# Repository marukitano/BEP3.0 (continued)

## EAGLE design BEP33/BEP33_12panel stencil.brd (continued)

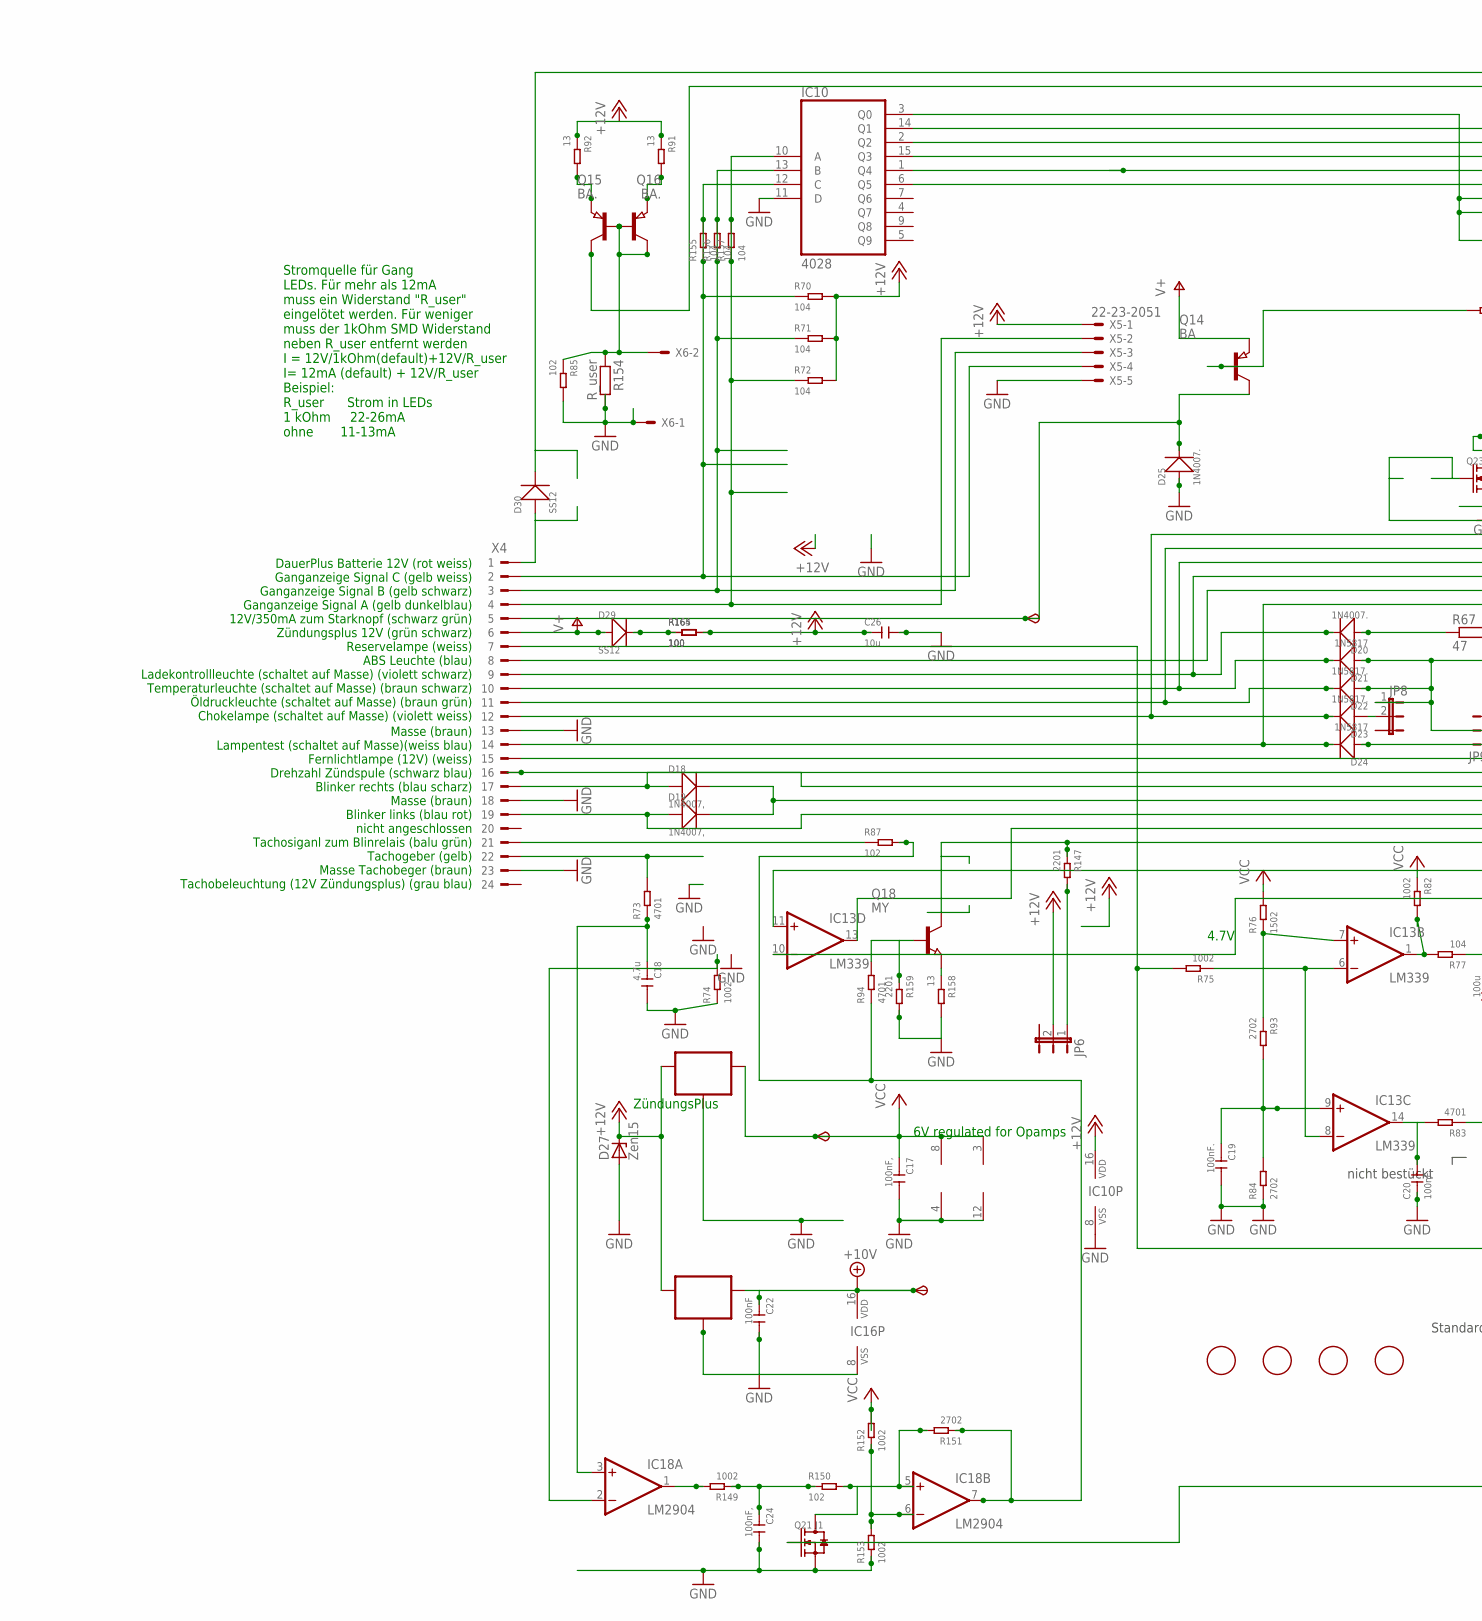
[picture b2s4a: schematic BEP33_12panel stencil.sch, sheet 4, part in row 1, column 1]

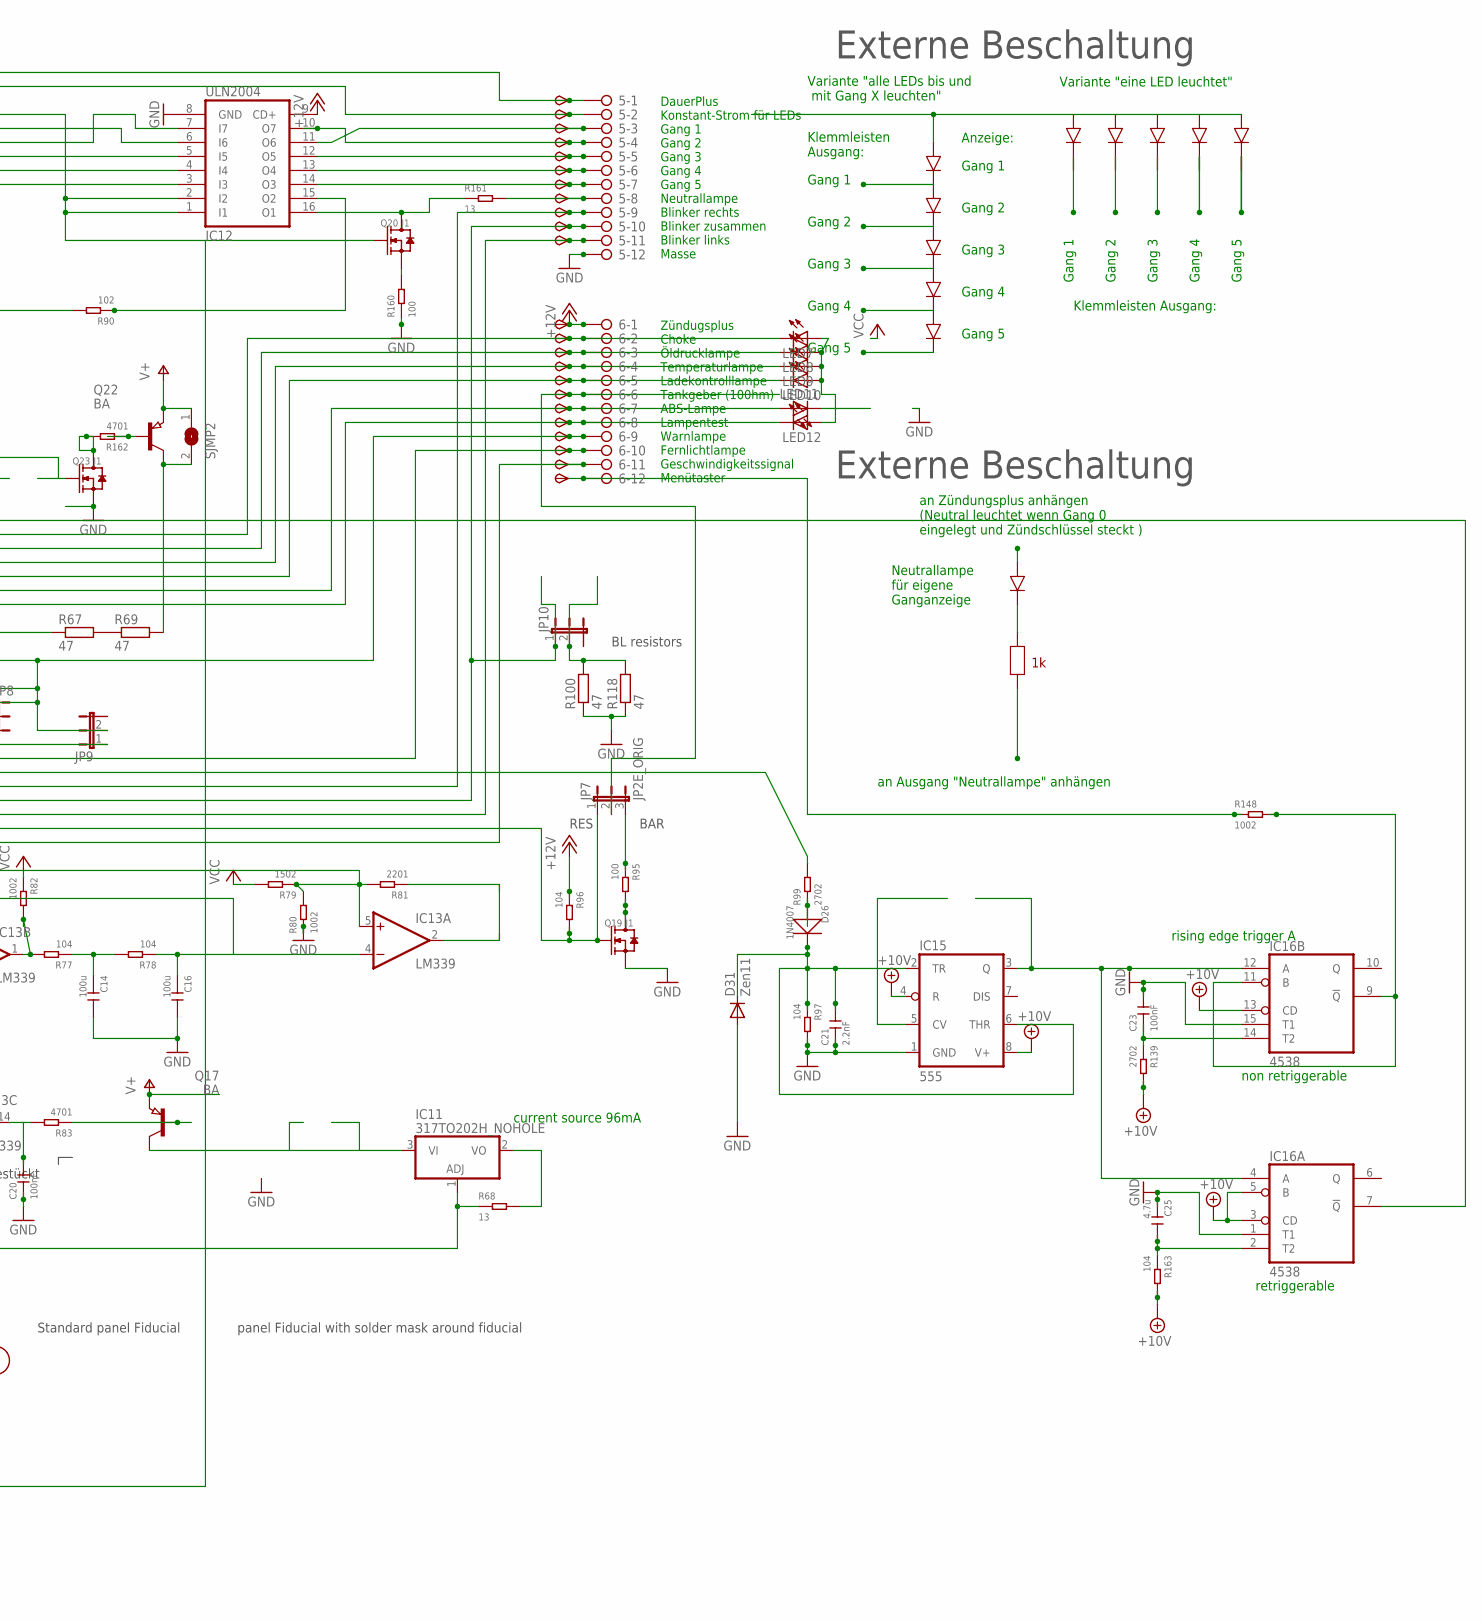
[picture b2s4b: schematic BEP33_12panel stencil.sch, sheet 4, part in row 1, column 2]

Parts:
5, 6: 2081-1132; 12-PIN
6V2, 10V2: TPSB2.0; B2.0
C14, C16: 100u; C1206
C17, C24: 100nF,; C0805
C18, C25: 4.7u; C0805
C19, C20: 100nF.; C0805
C21: 2.2nF; C0805
C22, C23: 100nF; C0805
C26: 10u; C1206
D18, D19: 1N4007,; DO-214AC
D20, D25: 1N4007.; DO-214AC
D21, D24: 1N5817; DO-214AC_SLIM
D22, D23: 1N5817.; DO-214AC_SLIM
D26: 1N4007; DO-214AC
D27: Zen15; DO214AA
D29, D30: SS12; DO-214AC_SLIM
D31: Zen11; SOD-123_MINI-SMA
FID7, FID8, FID9, FID10: FIDUCIAL; FIDUCIAL_1MM
IC10: 4028; SO16
IC11: 317TO202H_NOHOLE; TO220H_NOHOLE
IC12: ULN2004; SO16
IC13: LM339; SO14
IC14: 78L06; SOT89_ROUND
IC15: 555; SO08
IC16: 4538; SO16
IC17: 78L10; SOT89_ROUND
IC18: LM2904; SO08
JP6, JP8, JP9, JP10: JP2EJP2_SMALLPADS; JP2_SMALLPADS
JP7: JP2E_ORIG; JP2_ORIG_SMALLPADS
LED7, LED8, LED9, LED10, LED11, LED12: LEDLD260; LD260
Q14, Q17, Q22: BA; SOT89
Q15, Q16: BA.; SOT89
Q18: MY; SOT89
Q19, Q20, Q21, Q23: J1; SOT-23
R67, R69, R100, R118: 47; V235/17_1MM
R68, R91, R92, R158, R161: 13; R1206
R70, R71, R72, R77, R78, R96, R97, R155, R156, R157, R163: 104; R0805
R73, R83, R94, R162: 4701; R0805
R74, R75, R80, R82, R148, R149, R152, R153: 1002; R0805
R76, R79: 1502; R0805
R81, R147, R159: 2201; R0805
R84, R93, R99, R139, R151: 2702; R0805
R85, R87, R90, R150: 102; R0805
R95, R160, R164, R165: 100; R0805
R154: R_user; R0805
SJMP2: SJ
START2: TPSB2.0; B2.0
TP47, TP48, TP49, TP50, TP51, TP52, TP53, TP54, TP55, TP56, TP57, TP58, TP59, TP60, TP61, TP62, TP63, TP64, TP66, TP67, TP68, TP69: TPSB2.0; B2.0
TP65: TPSB1,27; B1,27
X4: CON_BMWV2; 24-PIN_V2
X5: 22-23-2051
X6: 22-23-2021

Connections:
+10V: 10V2.TP, C22.1, IC15.4 (R), IC15.8 (V+), IC16.3 (CD), IC16.5 (B), IC16.13 (CD), IC16.16 (VDD), IC17.1 (OUT), R139.2, R163.2; also elsewhere on the board
+12V: 6.1, C26.1, D27.C, IC10.16 (VDD), IC12.9 (CD+), IC14.3 (IN), IC17.3 (IN), JP6.2, R70.2, R71.2, R72.2, R91.1, R92.1, R96.1, R164.2, R165.2, TP68.TP, X5.1; also elsewhere on the board
+12V3: 6.11, Q18.2 (C), R147.1, TP67.TP
GND: 5.12, C14.2, C16.2, C17.2, C18.2, C19.2, C20.1, C21.1, C22.2, C23.2, C24.2, C25.1, C26.2, D25.1 (+), D27.A, D31.A, IC10.8 (VSS), IC10.11 (D), IC12.8 (GND), IC13.12 (GND), IC14.2 (GND), IC14.2@1 (GND), IC15.1 (GND), IC16.1 (T1), IC16.8 (VSS), IC16.15 (T1), IC17.2 (GND), IC17.2@1 (GND), IC18.4 (V-), Q19.2 (S), Q21.2 (S), Q23.2 (S), R74.1, R80.1, R84.1, R85.2, R97.2, R100.1, R118.1, R153.1, R154.2, R158.2, R159.2, R160.1, X4.13, X4.18, X4.23, X5.5, X6.1; also elsewhere on the board
unnamed: R67.2, R69.1
unnamed: 6.9, D21.1 (+), D22.1 (+), JP8.1, JP9.2, TP65.TP
unnamed: IC10.10 (A), R72.1, R157.1, R157.2, X4.4, X5.2
unnamed: IC10.13 (B), R71.1, R156.1, R156.2, X4.3, X5.3
unnamed: D25.2 (-), Q14.2 (C), START2.TP, X4.5
unnamed: IC10.12 (C), R70.1, R155.1, R155.2, X4.2, X5.4
unnamed: 6.7, LED11.A, TP63.TP, X4.8
unnamed: 6.2, D23.2 (-), LED7.K (C), TP58.TP, X4.12
unnamed: 6.3, D22.2 (-), LED8.K (C), TP59.TP, X4.11
unnamed: 6.4, D21.2 (-), LED9.K (C), TP60.TP, X4.10
unnamed: 6.8, D24.2 (-), LED12.K (C), TP64.TP, X4.14
unnamed: 5.9, D18.1 (+), TP55.TP, X4.17
unnamed: 5.11, D19.1 (+), TP57.TP, X4.19
unnamed: R73.2, X4.22
unnamed: C18.1, IC18.3 (+IN), R73.1
unnamed: IC13.1 (OUT), R77.2, R82.2
unnamed: C14.1, R77.1, R78.2
unnamed: C16.1, IC13.4 (-IN), IC13.10 (-IN), R78.1
unnamed: IC13.5 (+IN), IC13.11 (+IN), R79.1, R80.2, R81.2
unnamed: C19.1, IC13.9 (+IN), R84.2, R93.2
unnamed: C20.2, IC13.14 (OUT), R83.2
unnamed: Q17.1 (B), R83.1
unnamed: IC10.2 (Q2), IC12.7 (I7)
unnamed: 5.5, IC12.12 (O5), TP51.TP
unnamed: IC10.1 (Q4), IC12.4 (I4)
unnamed: 6.10, TP66.TP, X4.15
unnamed: 6.5, D20.2 (-), LED10.K (C), TP61.TP, X4.9
unnamed: D20.1 (+), R67.1
unnamed: IC10.6 (Q5), IC12.3 (I3)
unnamed: 5.4, IC12.10 (O7), TP50.TP
unnamed: IC11.1 (ADJ), R68.1, R75.2, X4.7
unnamed: IC13.6 (-IN), IC13.8 (-IN), R75.1
unnamed: 5.2, Q16.2 (C), TP48.TP
unnamed: 5.1, D30.2 (-), TP47.TP
unnamed: R99.2, X4.16
unnamed: IC10.15 (Q3), IC12.5 (I5)
unnamed: 5.6, IC12.13 (O4), TP52.TP
unnamed: 5.7, IC12.14 (O3), TP53.TP
unnamed: 6.6, JP7.2, TP62.TP
unnamed: LED7.A, LED8.A, LED9.A, LED10.A, LED12.A
unnamed: Q14.1 (B), R90.2
unnamed: IC10.3 (Q0), IC12.1 (I1), IC12.2 (I2), Q20.1 (G), Q21.1 (G)
unnamed: IC10.14 (Q1), IC12.6 (I6)
unnamed: 5.3, IC12.11 (O6), TP49.TP
unnamed: Q15.1 (B), Q15.2 (C), Q16.1 (B), R85.1, R154.1, X6.2
unnamed: Q16.3 (E), R92.2
unnamed: Q15.3 (E), R91.2
unnamed: IC13.7 (+IN), R76.1, R93.1
unnamed: IC18.2 (-IN), R74.2
unnamed: Q18.1 (B), R94.2, R159.1
unnamed: Q19.3 (D), R95.2
unnamed: IC11.2 (VO), R68.2
unnamed: IC11.3 (VI), Q17.2 (C)
unnamed: IC15.3 (Q), IC16.4 (A), IC16.12 (A)
unnamed: D26.1 (+), R99.1
unnamed: 5.10, D18.2 (-), D19.2 (-), JP10.1, TP56.TP
unnamed: JP10.2, R100.2, R118.2
unnamed: IC16.9 (!Q), IC16.11 (B), R148.2
unnamed: C23.1, IC16.14 (T2), R139.1
unnamed: JP6.1, R147.2
unnamed: IC12.15 (O2), R90.1
unnamed: 6.12, R148.1, TP69.TP
unnamed: D23.1 (+), JP8.2
unnamed: IC18.1 (OUT), R149.2
unnamed: C24.1, R149.1, R150.1
unnamed: IC18.5 (+IN), Q21.3 (D), R150.2, R151.2
unnamed: IC18.6 (-IN), R152.1, R153.2
unnamed: D24.1 (+), JP9.1
unnamed: JP7.3, R95.1
unnamed: IC13.13 (OUT), JP7.1, Q19.1 (G), R96.2
unnamed: R87.1, X4.21
unnamed: IC12.16 (O1), Q20.3 (D), R161.1
unnamed: D29.2 (-), R164.1, R165.1
unnamed: 5.8, R161.2, TP54.TP
unnamed: Q20.2 (S), R160.2
unnamed: D30.1 (+), X4.1
unnamed: Q18.3 (E), R158.1
unnamed: C21.2, D26.2 (-), D31.C, IC15.2 (TR), IC15.6 (THR), R97.1
unnamed: Q22.1 (B), R162.1
unnamed: Q23.3 (D), R162.2
unnamed: Q22.2 (C), R69.2, SJMP2.2
unnamed: IC18.7 (OUT), R87.2, R94.1, R151.1
unnamed: IC13.2 (OUT), R81.1
unnamed: IC16.7 (!Q), Q23.1 (G)
unnamed: C25.2, IC16.2 (T2), R163.1
V+: D29.1 (+), Q14.3 (E), Q17.3 (E), Q22.3 (E), SJMP2.1, X4.6; also elsewhere on the board
VCC: 6V2.TP, C17.1, IC13.3 (V+), IC14.1 (OUT), IC18.8 (V+), R76.2, R79.2, R82.1, R152.2; also elsewhere on the board

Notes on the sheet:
6V regulated for Opamps
current source 96mA
ZündungsPlus
Zündugsplus Choke Öldrucklampe Temperaturlampe Ladekontrolllampe Tankgeber (100hm) ABS-Lampe Lampentest Warnlampe Fernlichtlampe Geschwindigkeitssignal Menütaster
DauerPlus Konstant-Strom für LEDs Gang 1 Gang 2 Gang 3 Gang 4 Gang 5 Neutrallampe Blinker rechts Blinker zusammen Blinker links Masse
DauerPlus Batterie 12V (rot weiss) Ganganzeige Signal C (gelb weiss) Ganganzeige Signal B (gelb schwarz) Ganganzeige Signal A (gelb dunkelblau) 12V/350mA zum Starknopf (schwarz grün) Zündungsplus 12V (grün schwarz) Reservelampe (weiss) ABS Leuchte (blau) Ladekontrollleuchte (schaltet auf Masse) (vi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
Masse (braun) Lampentest (schaltet auf Masse)(weiss blau) Fernlichtlampe (12V) (weiss) Drehzahl Zündspule (schwarz blau) Blinker rechts (blau scharz) Masse (braun) Blinker links (blau rot) nicht angeschlossen Tachosiganl zum Blinrelais (balu grün) Tachogeber (gelb) Masse Tachobeger (braun) Tachobel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
4.7V
Stromquelle für Gang LEDs. Für mehr als 12mA muss ein Widerstand "R_user" eingelötet werden. Für weniger muss der 1kOhm SMD Widerstand neben R_user entfernt werden I = 12V/1kOhm(default)+12V/R_user I= 12mA (default) + 12V/R_user Beispiel: R_user Strom in LEDs 1 kOhm 22-26mA ohne 11-13mA
Gang 1
Gang 2
Gang 3
Gang 4
Gang 5
Variante "eine LED leuchtet"
Variante "alle LEDs bis und mit Gang X leuchten"
Klemmleisten Ausgang:
Klemmleisten Ausgang:
an Zündungsplus anhängen (Neutral leuchtet wenn Gang 0 eingelegt und Zündschlüssel steckt )
an Ausgang "Neutrallampe" anhängen
Neutrallampe für eigene Ganganzeige
Externe Beschaltung
Anzeige:
nicht bestückt
rising edge trigger A
BAR
RES
BL resistors
Standard panel Fiducial
panel Fiducial with solder mask around fiducial
non retriggerable
retriggerable

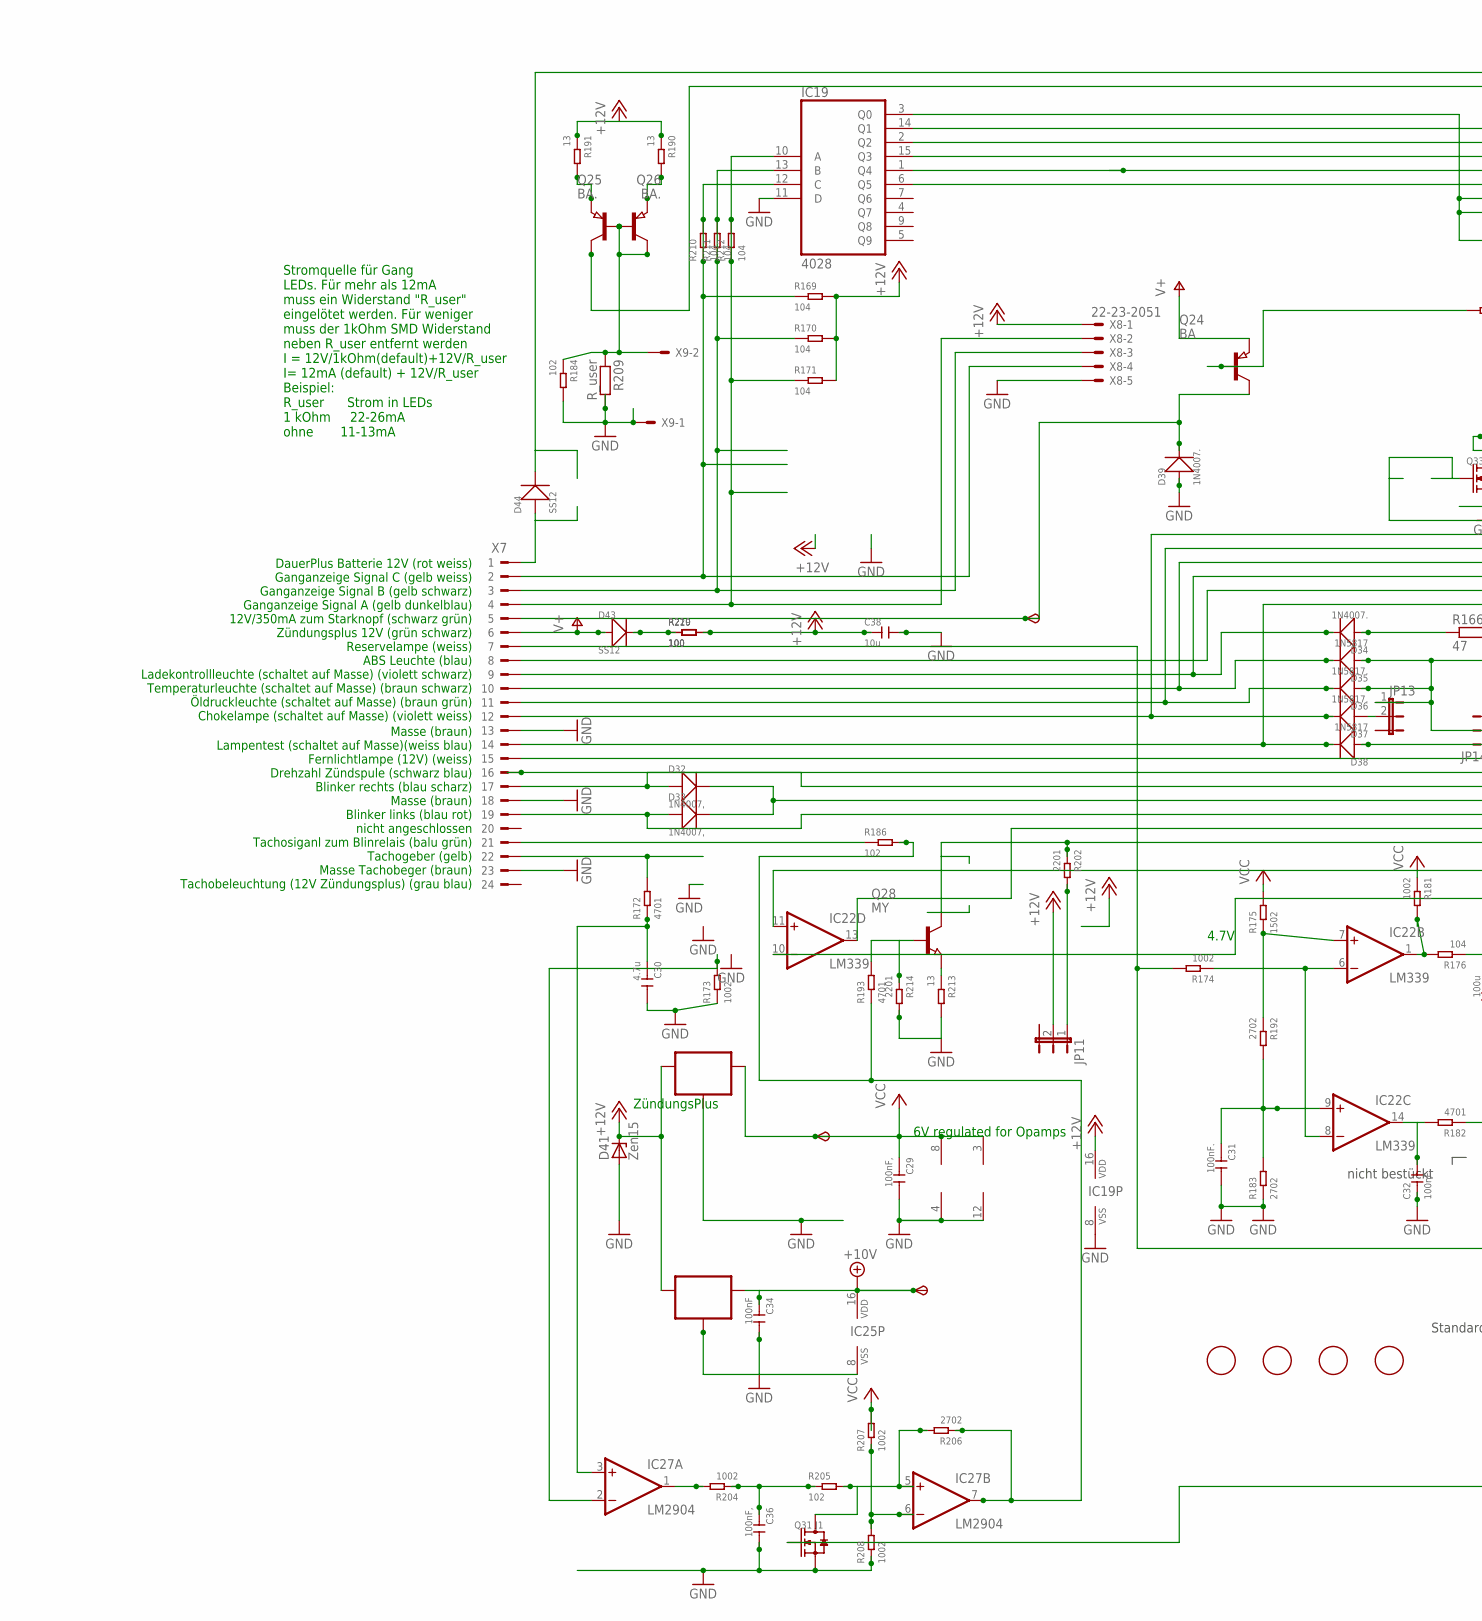
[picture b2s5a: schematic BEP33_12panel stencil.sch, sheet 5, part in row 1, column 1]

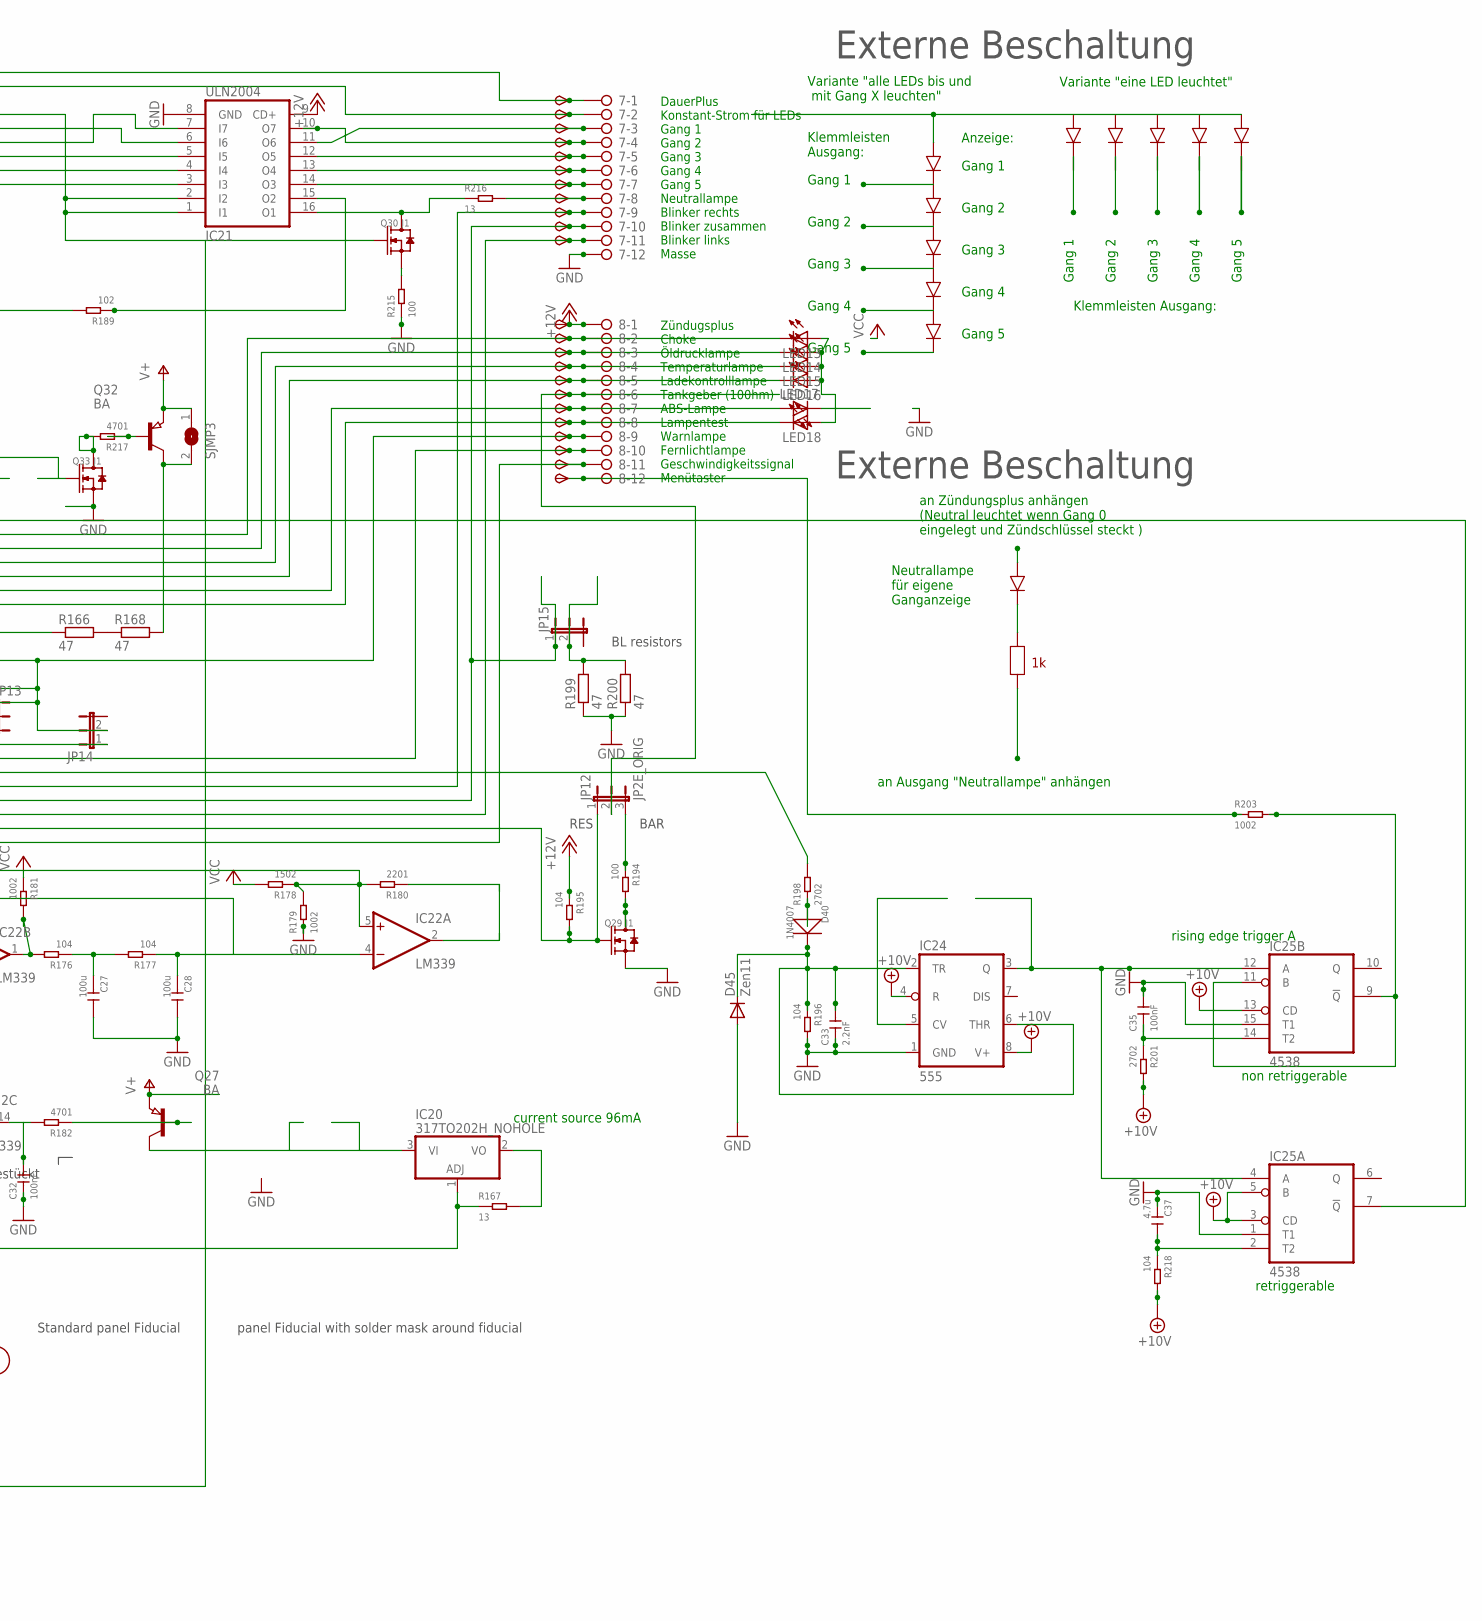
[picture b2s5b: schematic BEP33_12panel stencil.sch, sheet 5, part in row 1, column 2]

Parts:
6V3, 10V3: TPSB2.0; B2.0
7, 8: 2081-1132; 12-PIN
C27, C28: 100u; C1206
C29, C36: 100nF,; C0805
C30, C37: 4.7u; C0805
C31, C32: 100nF.; C0805
C33: 2.2nF; C0805
C34, C35: 100nF; C0805
C38: 10u; C1206
D32, D33: 1N4007,; DO-214AC
D34, D39: 1N4007.; DO-214AC
D35, D38: 1N5817; DO-214AC_SLIM
D36, D37: 1N5817.; DO-214AC_SLIM
D40: 1N4007; DO-214AC
D41: Zen15; DO214AA
D43, D44: SS12; DO-214AC_SLIM
D45: Zen11; SOD-123_MINI-SMA
FID11, FID12, FID13, FID14: FIDUCIAL; FIDUCIAL_1MM
IC19: 4028; SO16
IC20: 317TO202H_NOHOLE; TO220H_NOHOLE
IC21: ULN2004; SO16
IC22: LM339; SO14
IC23: 78L06; SOT89_ROUND
IC24: 555; SO08
IC25: 4538; SO16
IC26: 78L10; SOT89_ROUND
IC27: LM2904; SO08
JP11, JP13, JP14, JP15: JP2EJP2_SMALLPADS; JP2_SMALLPADS
JP12: JP2E_ORIG; JP2_ORIG_SMALLPADS
LED13, LED14, LED15, LED16, LED17, LED18: LEDLD260; LD260
Q24, Q27, Q32: BA; SOT89
Q25, Q26: BA.; SOT89
Q28: MY; SOT89
Q29, Q30, Q31, Q33: J1; SOT-23
R166, R168, R199, R200: 47; V235/17_1MM
R167, R190, R191, R213, R216: 13; R1206
R169, R170, R171, R176, R177, R195, R196, R210, R211, R212, R218: 104; R0805
R172, R182, R193, R217: 4701; R0805
R173, R174, R179, R181, R203, R204, R207, R208: 1002; R0805
R175, R178: 1502; R0805
R180, R202, R214: 2201; R0805
R183, R192, R198, R201, R206: 2702; R0805
R184, R186, R189, R205: 102; R0805
R194, R215, R219, R220: 100; R0805
R209: R_user; R0805
SJMP3: SJ
START3: TPSB2.0; B2.0
TP70, TP71, TP72, TP73, TP74, TP75, TP76, TP77, TP78, TP79, TP80, TP81, TP82, TP83, TP84, TP85, TP86, TP87, TP89, TP90, TP91, TP92: TPSB2.0; B2.0
TP88: TPSB1,27; B1,27
X7: CON_BMWV2; 24-PIN_V2
X8: 22-23-2051
X9: 22-23-2021

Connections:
+10V: 10V3.TP, C34.1, IC24.4 (R), IC24.8 (V+), IC25.3 (CD), IC25.5 (B), IC25.13 (CD), IC25.16 (VDD), IC26.1 (OUT), R201.2, R218.2; also elsewhere on the board
+12V: 8.1, C38.1, D41.C, IC19.16 (VDD), IC21.9 (CD+), IC23.3 (IN), IC26.3 (IN), JP11.2, R169.2, R170.2, R171.2, R190.1, R191.1, R195.1, R219.2, R220.2, TP91.TP, X8.1; also elsewhere on the board
+12V4: 8.11, Q28.2 (C), R202.1, TP90.TP
GND: 7.12, C27.2, C28.2, C29.2, C30.2, C31.2, C32.1, C33.1, C34.2, C35.2, C36.2, C37.1, C38.2, D39.1 (+), D41.A, D45.A, IC19.8 (VSS), IC19.11 (D), IC21.8 (GND), IC22.12 (GND), IC23.2 (GND), IC23.2@1 (GND), IC24.1 (GND), IC25.1 (T1), IC25.8 (VSS), IC25.15 (T1), IC26.2 (GND), IC26.2@1 (GND), IC27.4 (V-), Q29.2 (S), Q31.2 (S), Q33.2 (S), R173.1, R179.1, R183.1, R184.2, R196.2, R199.1, R200.1, R208.1, R209.2, R213.2, R214.2, R215.1, X7.13, X7.18, X7.23, X8.5, X9.1; also elsewhere on the board
unnamed: R166.2, R168.1
unnamed: 8.9, D35.1 (+), D36.1 (+), JP13.1, JP14.2, TP88.TP
unnamed: IC19.10 (A), R171.1, R212.1, R212.2, X7.4, X8.2
unnamed: IC19.13 (B), R170.1, R211.1, R211.2, X7.3, X8.3
unnamed: D39.2 (-), Q24.2 (C), START3.TP, X7.5
unnamed: IC19.12 (C), R169.1, R210.1, R210.2, X7.2, X8.4
unnamed: 8.7, LED17.A, TP86.TP, X7.8
unnamed: 8.2, D37.2 (-), LED13.K (C), TP81.TP, X7.12
unnamed: 8.3, D36.2 (-), LED14.K (C), TP82.TP, X7.11
unnamed: 8.4, D35.2 (-), LED15.K (C), TP83.TP, X7.10
unnamed: 8.8, D38.2 (-), LED18.K (C), TP87.TP, X7.14
unnamed: 7.9, D32.1 (+), TP78.TP, X7.17
unnamed: 7.11, D33.1 (+), TP80.TP, X7.19
unnamed: R172.2, X7.22
unnamed: C30.1, IC27.3 (+IN), R172.1
unnamed: IC22.1 (OUT), R176.2, R181.2
unnamed: C27.1, R176.1, R177.2
unnamed: C28.1, IC22.4 (-IN), IC22.10 (-IN), R177.1
unnamed: IC22.5 (+IN), IC22.11 (+IN), R178.1, R179.2, R180.2
unnamed: C31.1, IC22.9 (+IN), R183.2, R192.2
unnamed: C32.2, IC22.14 (OUT), R182.2
unnamed: Q27.1 (B), R182.1
unnamed: IC19.2 (Q2), IC21.7 (I7)
unnamed: 7.5, IC21.12 (O5), TP74.TP
unnamed: IC19.1 (Q4), IC21.4 (I4)
unnamed: 8.10, TP89.TP, X7.15
unnamed: 8.5, D34.2 (-), LED16.K (C), TP84.TP, X7.9
unnamed: D34.1 (+), R166.1
unnamed: IC19.6 (Q5), IC21.3 (I3)
unnamed: 7.4, IC21.10 (O7), TP73.TP
unnamed: IC20.1 (ADJ), R167.1, R174.2, X7.7
unnamed: IC22.6 (-IN), IC22.8 (-IN), R174.1
unnamed: 7.2, Q26.2 (C), TP71.TP
unnamed: 7.1, D44.2 (-), TP70.TP
unnamed: R198.2, X7.16
unnamed: IC19.15 (Q3), IC21.5 (I5)
unnamed: 7.6, IC21.13 (O4), TP75.TP
unnamed: 7.7, IC21.14 (O3), TP76.TP
unnamed: 8.6, JP12.2, TP85.TP
unnamed: LED13.A, LED14.A, LED15.A, LED16.A, LED18.A
unnamed: Q24.1 (B), R189.2
unnamed: IC19.3 (Q0), IC21.1 (I1), IC21.2 (I2), Q30.1 (G), Q31.1 (G)
unnamed: IC19.14 (Q1), IC21.6 (I6)
unnamed: 7.3, IC21.11 (O6), TP72.TP
unnamed: Q25.1 (B), Q25.2 (C), Q26.1 (B), R184.1, R209.1, X9.2
unnamed: Q26.3 (E), R191.2
unnamed: Q25.3 (E), R190.2
unnamed: IC22.7 (+IN), R175.1, R192.1
unnamed: IC27.2 (-IN), R173.2
unnamed: Q28.1 (B), R193.2, R214.1
unnamed: Q29.3 (D), R194.2
unnamed: IC20.2 (VO), R167.2
unnamed: IC20.3 (VI), Q27.2 (C)
unnamed: IC24.3 (Q), IC25.4 (A), IC25.12 (A)
unnamed: D40.1 (+), R198.1
unnamed: 7.10, D32.2 (-), D33.2 (-), JP15.1, TP79.TP
unnamed: JP15.2, R199.2, R200.2
unnamed: IC25.9 (!Q), IC25.11 (B), R203.2
unnamed: C35.1, IC25.14 (T2), R201.1
unnamed: JP11.1, R202.2
unnamed: IC21.15 (O2), R189.1
unnamed: 8.12, R203.1, TP92.TP
unnamed: D37.1 (+), JP13.2
unnamed: IC27.1 (OUT), R204.2
unnamed: C36.1, R204.1, R205.1
unnamed: IC27.5 (+IN), Q31.3 (D), R205.2, R206.2
unnamed: IC27.6 (-IN), R207.1, R208.2
unnamed: D38.1 (+), JP14.1
unnamed: JP12.3, R194.1
unnamed: IC22.13 (OUT), JP12.1, Q29.1 (G), R195.2
unnamed: R186.1, X7.21
unnamed: IC21.16 (O1), Q30.3 (D), R216.1
unnamed: D43.2 (-), R219.1, R220.1
unnamed: 7.8, R216.2, TP77.TP
unnamed: Q30.2 (S), R215.2
unnamed: D44.1 (+), X7.1
unnamed: Q28.3 (E), R213.1
unnamed: C33.2, D40.2 (-), D45.C, IC24.2 (TR), IC24.6 (THR), R196.1
unnamed: Q32.1 (B), R217.1
unnamed: Q33.3 (D), R217.2
unnamed: Q32.2 (C), R168.2, SJMP3.2
unnamed: IC27.7 (OUT), R186.2, R193.1, R206.1
unnamed: IC22.2 (OUT), R180.1
unnamed: IC25.7 (!Q), Q33.1 (G)
unnamed: C37.2, IC25.2 (T2), R218.1
V+: D43.1 (+), Q24.3 (E), Q27.3 (E), Q32.3 (E), SJMP3.1, X7.6; also elsewhere on the board
VCC: 6V3.TP, C29.1, IC22.3 (V+), IC23.1 (OUT), IC27.8 (V+), R175.2, R178.2, R181.1, R207.2; also elsewhere on the board

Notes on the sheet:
6V regulated for Opamps
current source 96mA
ZündungsPlus
Zündugsplus Choke Öldrucklampe Temperaturlampe Ladekontrolllampe Tankgeber (100hm) ABS-Lampe Lampentest Warnlampe Fernlichtlampe Geschwindigkeitssignal Menütaster
DauerPlus Konstant-Strom für LEDs Gang 1 Gang 2 Gang 3 Gang 4 Gang 5 Neutrallampe Blinker rechts Blinker zusammen Blinker links Masse
DauerPlus Batterie 12V (rot weiss) Ganganzeige Signal C (gelb weiss) Ganganzeige Signal B (gelb schwarz) Ganganzeige Signal A (gelb dunkelblau) 12V/350mA zum Starknopf (schwarz grün) Zündungsplus 12V (grün schwarz) Reservelampe (weiss) ABS Leuchte (blau) Ladekontrollleuchte (schaltet auf Masse) (vi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
Masse (braun) Lampentest (schaltet auf Masse)(weiss blau) Fernlichtlampe (12V) (weiss) Drehzahl Zündspule (schwarz blau) Blinker rechts (blau scharz) Masse (braun) Blinker links (blau rot) nicht angeschlossen Tachosiganl zum Blinrelais (balu grün) Tachogeber (gelb) Masse Tachobeger (braun) Tachobel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
4.7V
Stromquelle für Gang LEDs. Für mehr als 12mA muss ein Widerstand "R_user" eingelötet werden. Für weniger muss der 1kOhm SMD Widerstand neben R_user entfernt werden I = 12V/1kOhm(default)+12V/R_user I= 12mA (default) + 12V/R_user Beispiel: R_user Strom in LEDs 1 kOhm 22-26mA ohne 11-13mA
Gang 1
Gang 2
Gang 3
Gang 4
Gang 5
Variante "eine LED leuchtet"
Variante "alle LEDs bis und mit Gang X leuchten"
Klemmleisten Ausgang:
Klemmleisten Ausgang:
an Zündungsplus anhängen (Neutral leuchtet wenn Gang 0 eingelegt und Zündschlüssel steckt )
an Ausgang "Neutrallampe" anhängen
Neutrallampe für eigene Ganganzeige
Externe Beschaltung
Anzeige:
nicht bestückt
rising edge trigger A
BAR
RES
BL resistors
Standard panel Fiducial
panel Fiducial with solder mask around fiducial
non retriggerable
retriggerable
